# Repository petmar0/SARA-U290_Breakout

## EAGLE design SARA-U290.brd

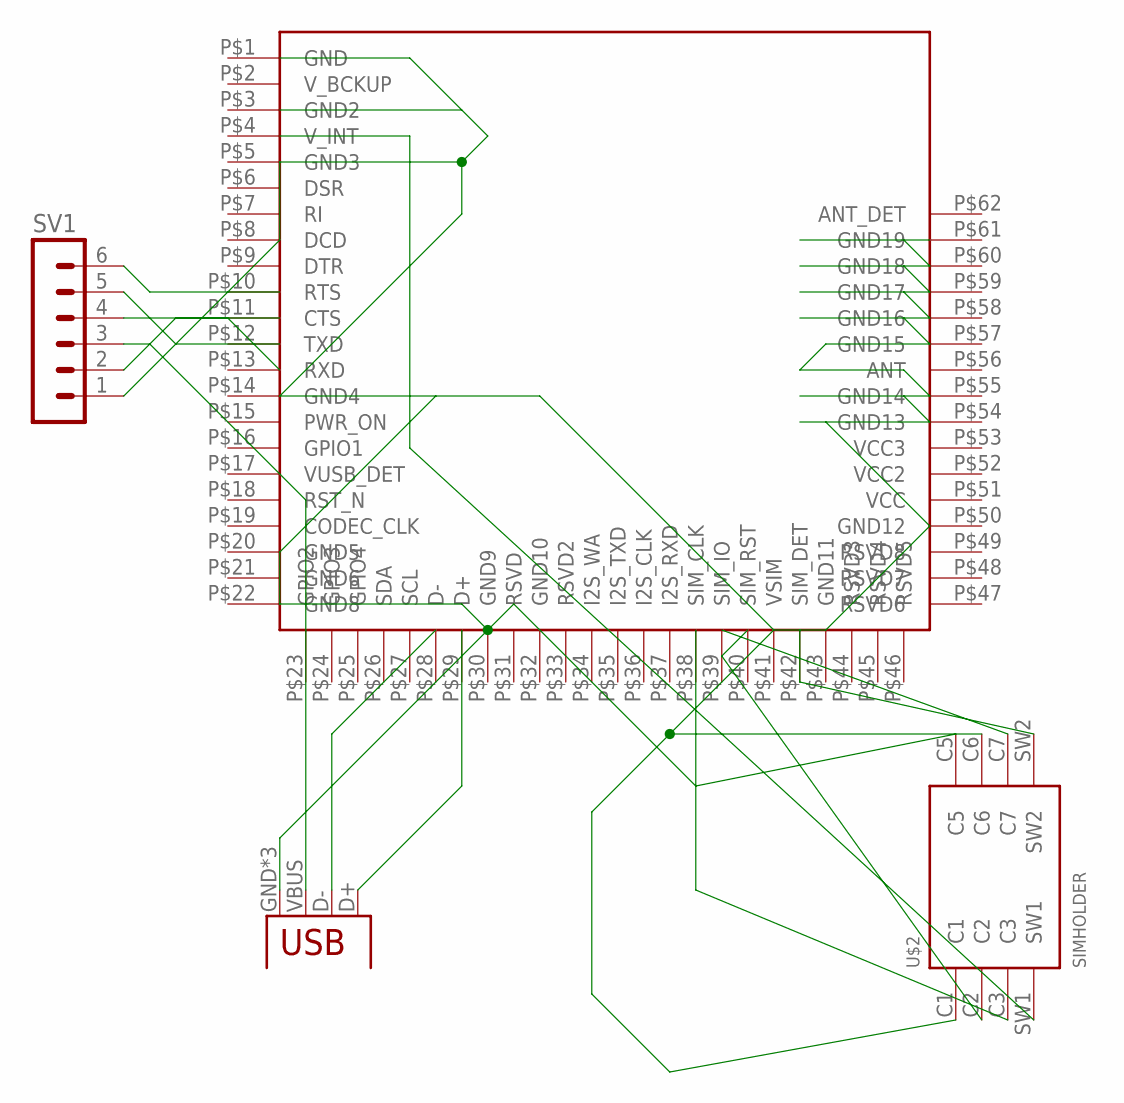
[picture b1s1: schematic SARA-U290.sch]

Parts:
JP1: USB-MICROB
SV1: MA06-1
U$1: SARA-U290
U$2: SIMHOLDER

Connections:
unnamed: U$2.C1, U$2.C6
unnamed: JP1.GND, JP1.MT1 (GND), JP1.MT2 (GND), SV1.1, U$2.C5
unnamed: JP1.VBUS, SV1.3

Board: 2 copper layers, 4 parts (0 on the bottom side), 3 nets, no tracks yet.

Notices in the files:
parts and their libraries:
SparkFun-Connectors: Licensing: CC v3.0 Share-Alike You are welcome to use this library for commercial purposes.
